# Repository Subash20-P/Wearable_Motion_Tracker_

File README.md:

## Wearable Motion Tracker

A compact, battery-powered custom PCB designed in **KiCad** for wearable motion and barometric sensing, built around the **ESP32-C3** wireless microcontroller with integrated USB Type-C Li-Po charging and 3.3V power regulation.

## Visuals

## Hardware Architecture

* **Microcontroller & RF Link (`U1` — ESP32-C3):** Handles wireless telemetry and sensor processing with a cleared antenna keep-out zone along the board edge.
* **6-Axis Inertial Sensing (`U2` — MPU-6050):** Measures 3-axis acceleration and 3-axis angular velocity over the shared I2C bus (`SDA`, `SCL` with `4.7k` pull-up resistors).
* **Barometric & Environmental Sensing (`U3` — BMP280):** Provides barometric pressure, altitude estimation, and ambient temperature over I2C.
* **Battery & Charging Management (`J1`, `U4`, `BT1`, `SW1`):**
  * USB Type-C receptacle (`J1`) with `5.1k` CC configuration resistors (`R1`, `R2`)
  * `TP4056` (`U4`) single-cell Li-Po battery charger IC
  * Onboard battery cell connector (`BT1`) and physical power switch (`SW1`)
* **Voltage Regulation (`U5` — ME6211C33M5):** Steps down battery/input voltage to a regulated `3.3V` rail for the MCU and sensors with local decoupling capacitors (`C2`, `C3`, `C4`, `C6`).

## Conclusion

This project demonstrates the design and development of a wearable motion tracking PCB using ESP32
C3, MPU6050, and BMP280 sensors. The system is capable of tracking motion and vertical movement 
while maintaining compact size and low power operation suitable for wearable applications. The project 
also demonstrates embedded hardware design, sensor integration, battery management, and PCB 
development workflow.

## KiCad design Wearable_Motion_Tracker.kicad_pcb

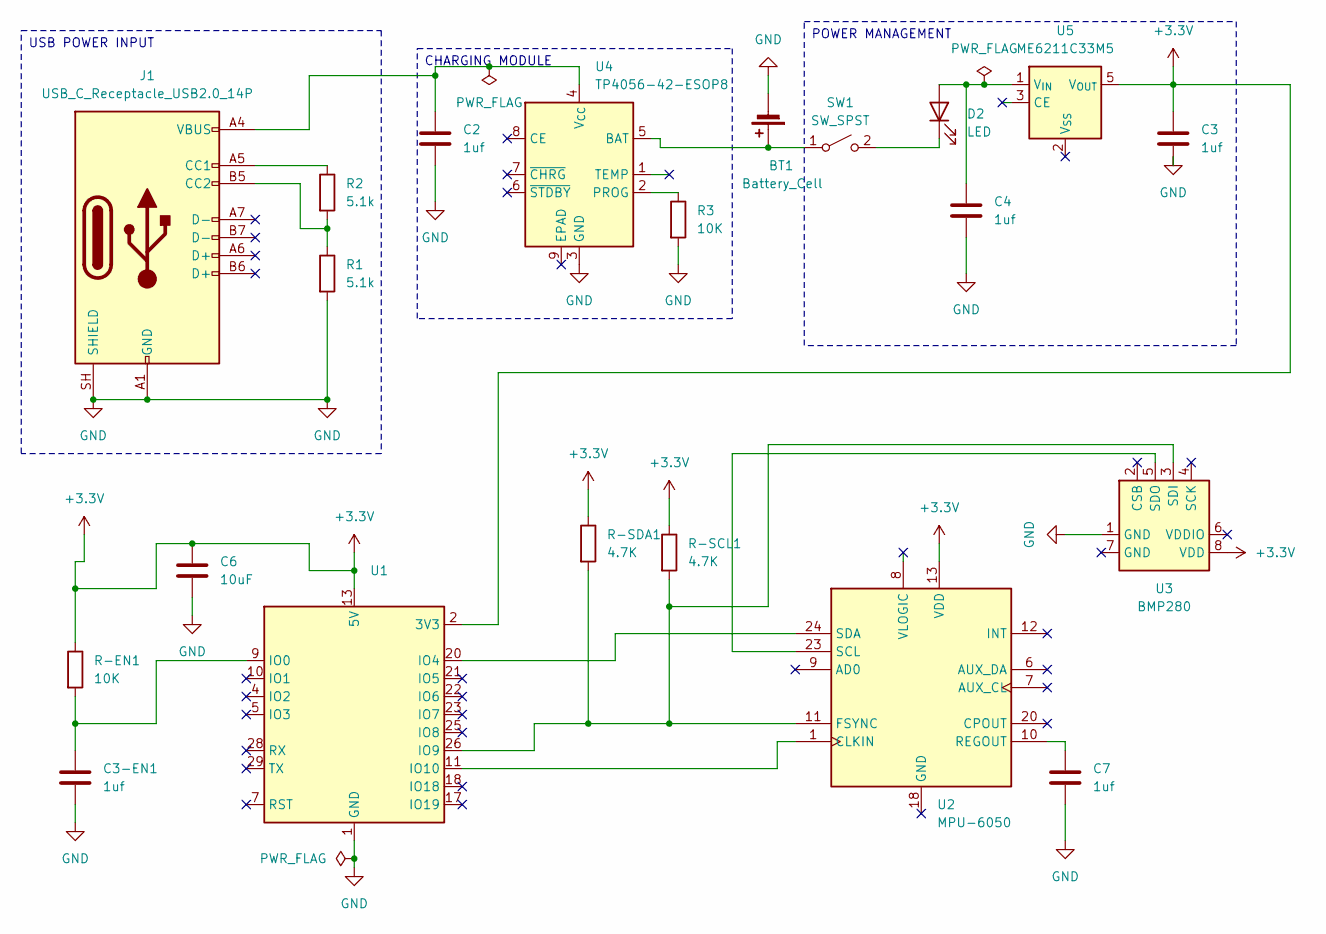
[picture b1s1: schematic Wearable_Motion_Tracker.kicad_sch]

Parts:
BT1: Battery_Cell; JST_PH_S2B-PH-K_1x02_P2.00mm_Horizontal
C2, C3, C3-EN1, C4, C7: 1uf; C_0603_1608Metric
C6: 10uF; C_0603_1608Metric
D2: LED; LED_0603_1608Metric
J1: USB_C_Receptacle_USB2.0_14P; USB_C_Receptacle_HRO_TYPE-C-31-M-12
R1, R2: 5.1k; R_0603_1608Metric
R3: 10K; R_0603_1608Metric
R-EN1: 10K; R_0603_1608Metric
R-SCL1: 4.7K; R_0603_1608Metric
R-SDA1: 4.7K; R_0603_1608Metric
SW1: SW_SPST; SW_SPDT_PCM12
U1: ESP32-C3-DevKitM-1
U2: MPU-6050; InvenSense_QFN-24_4x4mm_P0.5mm
U3: BMP280; Bosch_LGA-8_2x2.5mm_P0.65mm_ClockwisePinNumbering
U4: TP4056-42-ESOP8; SOIC-8-1EP_3.9x4.9mm_P1.27mm_EP2.41x3.3mm_ThermalVias
U5: ME6211C33M5; SOT-23-5

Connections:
+3.3V: C3.1, C6.1, R-EN1.1, R-SCL1.1, R-SDA1.1, U1.2 (3V3), U1.3 (3V3), U1.13 (5V), U1.14 (5V), U2.13 (VDD), U3.8 (VDD), U5.5 (V_{OUT})
GND: BT1.2 (-), C2.2, C3.2, C3-EN1.2, C4.2, C6.2, C7.2, J1.A1 (GND), J1.A12 (GND), J1.B1 (GND), J1.B12 (GND), J1.SH (SHIELD), R1.2, R3.2, U1.1 (GND), U1.6 (GND), U1.8 (GND), U1.12 (GND), U1.15 (GND), U1.16 (GND), U1.19 (GND), U1.24 (GND), U1.27 (GND), U1.30 (GND), U3.1 (GND), U4.3 (GND)
unnamed: BT1.1 (+), SW1.1 (A), U4.5 (BAT)
unnamed: C4.1, D2.2 (A), U5.1 (V_{IN})
unnamed: D2.1 (K), SW1.2 (B)
unnamed: J1.A5 (CC1), R2.1
unnamed: J1.B5 (CC2), R1.1, R2.2
unnamed: C3-EN1.1, R-EN1.2, U1.9 (IO0)
unnamed: U1.20 (IO4), U2.24 (SDA)
unnamed: R-SCL1.2, R-SDA1.2, U1.26 (IO9), U2.11 (FSYNC), U3.3 (SDI)
unnamed: U1.11 (IO10), U2.1 (CLKIN)
unnamed: C7.1, U2.10 (REGOUT)
unnamed: U2.23 (SCL), U3.5 (SDO)
unnamed: R3.1, U4.2 (PROG)
unnamed: C2.1, J1.A4 (VBUS), J1.A9 (VBUS), J1.B4 (VBUS), J1.B9 (VBUS), U4.4 (V_{CC})

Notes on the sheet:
POWER MANAGEMENT
USB POWER INPUT
CHARGING MODULE

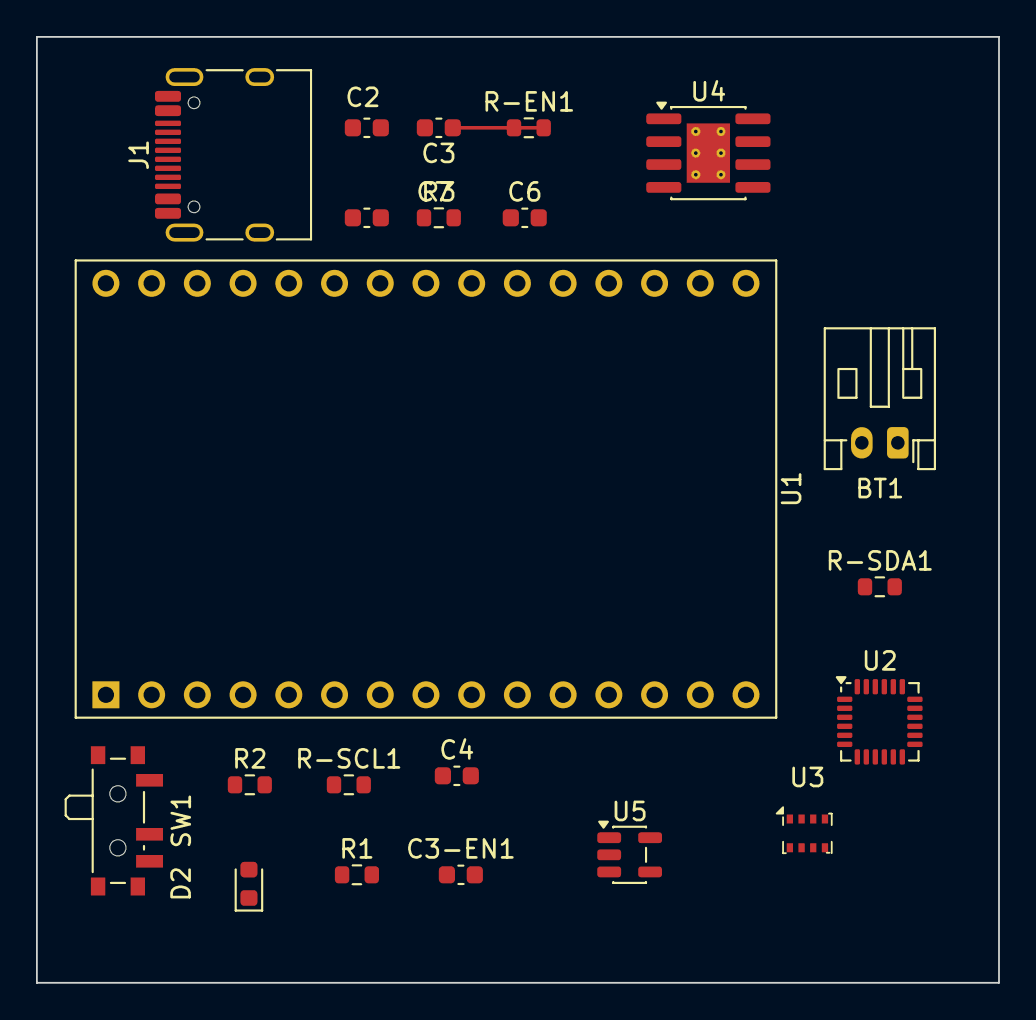
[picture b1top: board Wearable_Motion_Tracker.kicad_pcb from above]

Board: 2 copper layers, 53.5 x 52.6 mm, 21 parts (0 on the bottom side), 15 nets.
